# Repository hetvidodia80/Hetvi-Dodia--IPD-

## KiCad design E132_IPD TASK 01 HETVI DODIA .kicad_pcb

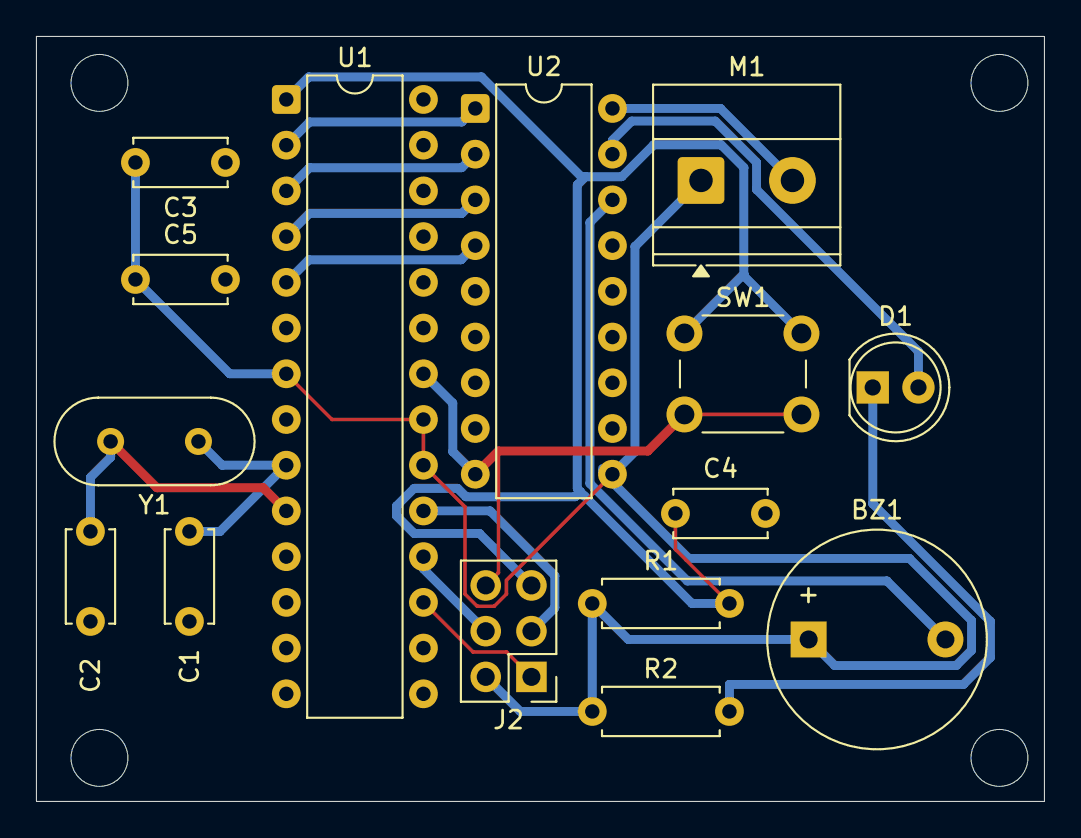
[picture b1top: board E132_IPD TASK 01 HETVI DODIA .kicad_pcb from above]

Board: 2 copper layers, 56.0 x 42.5 mm, 15 parts (0 on the bottom side), 16 nets.

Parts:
BZ1: Buzzer; Buzzer_12x9.5RM7.6
C1, C2: 22pF; C_Disc_D5.0mm_W2.5mm_P5.00mm
C3: 0.5uF; C_Disc_D5.0mm_W2.5mm_P5.00mm
C4: 100n; C_Disc_D5.0mm_W2.5mm_P5.00mm
C5: 0.1uF; C_Disc_D5.0mm_W2.5mm_P5.00mm
D1: LED; LED_D5.0mm
J2: Conn_02x03_Odd_Even; PinHeader_2x03_P2.54mm_Vertical
M1: Motor_DC; TerminalBlock_Phoenix_MKDS-1,5-2-5.08_1x02_P5.08mm_Horizont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
R1: 10k; R_Axial_DIN0207_L6.3mm_D2.5mm_P7.62mm_Horizontal
R2: 330; R_Axial_DIN0207_L6.3mm_D2.5mm_P7.62mm_Horizontal
SW1: SW_Push; SW_PUSH_6mm
U1: ATmega328P-P; DIP-28_W7.62mm
U2: ULN2803A; DIP-18_W7.62mm
Y1: Crystal; Crystal_HC49-U_Vertical

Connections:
GND: C1.1, C2.1, C3.1, C4.2, C5.2, J2.6, SW1.2, U1.8 (GND), U1.22 (GND), U2.9 (GND)
unnamed: BZ1.2 (-), U2.16 (O3)
unnamed: D1.2 (A), U2.17 (O2)
unnamed: D1.1 (K), R2.2
unnamed: J2.1, U1.17 (PB3)
unnamed: J2.3, U1.19 (PB5)
unnamed: J2.4, U1.18 (PB4)
unnamed: C4.1, J2.5, R1.2, SW1.1, U1.1 (~RESET/PC6)
unnamed: M1.2 (-), U2.18 (O1)
unnamed: U1.2 (PD0), U2.1 (I1)
unnamed: U1.3 (PD1), U2.2 (I2)
unnamed: U1.4 (PD2), U2.3 (I3)
unnamed: U1.5 (PD3), U2.4 (I4)
unnamed: C1.2, U1.9 (XTAL1/PB6), Y1.1
unnamed: C2.2, U1.10 (XTAL2/PB7), Y1.2
VCC: BZ1.1 (+), C3.2, C5.1, J2.2, M1.1 (+), R1.1, R2.1, U1.7 (VCC), U1.20 (AVCC), U1.21 (AREF), U2.10 (COM)
